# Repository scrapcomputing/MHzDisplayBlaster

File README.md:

# MHz Display Blaster

A clone of the TD-37S 2-digit MHz display that was common in 386/486 PC cases.
It can display a Turbo and a non-Turbo number, depending on the state of the Turbo switch.
It also drives the Turbo LED accordingly.

# Assembly Tips
- Video showing the assembly of rev.0.1 PCB: https://www.youtube.com/watch?v=a4iVehn7APU
> **Warning**
> Please solder the single-row header and the resistor *before* you solder the 7-segment display

# Connecting the board to the PC
- Power: The display is powered by providing 5V to the `+` pin of J4 and GND to the `-` pin.
- Turbo Switch: The turbo switch is a 3-pin 2-way switch. Connect the common wire (middle) to `CM`, the Turbo-ON wire to `T` and the Turbo-OFF wire to `N` (J4).
- Turbo LED: The turbo LED is connected to `L` and `P` on J4. `P` is the positive.

# Display Configuration
- Each segment of the 7-segment display is configured individually with a jumper
- Each segment corresponds to a pin in the configuration headers
- You can short that pin with one of the neighboring state pins (forming a `T` shape) to set its state, which can be one of the following:
  1. ON when Turbo switch is OFF (jumper to position 1)
  2. ON when Turbo switch is ON (jumper to position 2)
  3. Always ON (jumper to position 3)
  4. Always OFF (no jumper)

> **Note**
> Please note that the PCB is often mounted up side down on the case.

- For a simple tutorial on how to set it up please refer to the video: https://www.youtube.com/watch?v=wNkg-e47Ex8
- [More resources on MHz Displays](https://www.minuszerodegrees.net/led_speed_display/led_speed_display.htm)

# Bill of materials

Gerber files are published in the releases: https://github.com/scrapcomputing/MHzDisplayBlaster/releases

Reference      | Quantity| Value    | Footprint/Comments
---------------|---------|----------|----------
U1             | 1       |(e.g., LTD-6440G) | 18-DIP (0.600", 15.24mm distance between top and bottom row pins) 2-Digit 7-Segment Display Common Cathode 0.56" Green
J1 J2          | 2       |Conn_02x15| Connector Male PinHeader 2x15 P2.54mm Vertical
J4             | 1       |Conn_01x07| Connector Male PinHeader 1x07 P2.54mm Vertical
R1             | 1       | >= 39 Ohm (100 Ohms recommended)| 1/4 Watt resistor. The original TD37S has a 39 Ohm resistor. But the resistor value is specific to the type of the LEDs used. The original ones operate at around 2V, so the resistor drops 3V. Higher resistor values make the display more dim, but are also better for the longevity of the LEDs in the display.
Jumpers        | 15      |          | 2.54mm pitch jumpers

# Changelist
- Rev.0.2 : Fixes polarity issue, improves info
- Rev.0.1 : Initial revision

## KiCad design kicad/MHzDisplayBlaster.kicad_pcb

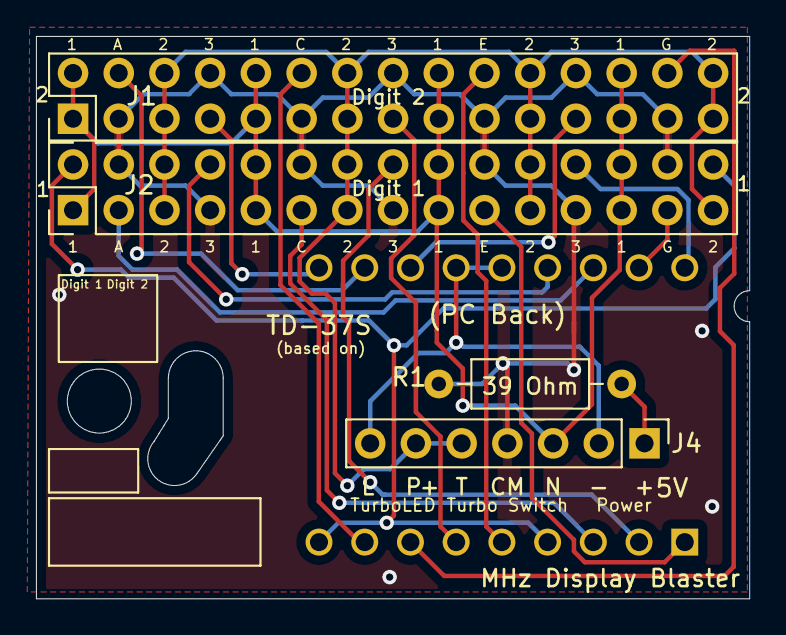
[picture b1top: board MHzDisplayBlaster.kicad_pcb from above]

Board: 2 copper layers, 39.6 x 31.2 mm, 5 parts (1 on the bottom side), 20 nets.

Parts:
J1: Conn_02x15 DigitRHS; PinHeader_2x15_P2.54mm_Vertical
J2: Conn_02x15 DigitLHS; PinHeader_2x15_P2.54mm_Vertical
J4: Conn_01x07; PinHeader_1x07_P2.54mm_Vertical
R1: 39 Ohm; R_Axial_DIN0207_L6.3mm_D2.5mm_P10.16mm_Horizontal
U1: DC56-11GWA; DA56-11CGKWA

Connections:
1: J1.1, J1.2, J1.9, J1.10, J1.17, J1.18, J1.25, J1.26, J2.1, J2.9, J2.10, J2.17, J2.18, J2.25, J2.26, J4.3
2: J1.5, J1.6, J1.13, J1.14, J1.21, J1.22, J1.29, J1.30, J2.5, J2.6, J2.13, J2.14, J2.21, J2.22, J2.29, J4.5, J4.6
3: J1.3, J1.8, J1.11, J1.16, J1.19, J1.24, J1.27, J2.4, J2.7, J2.12, J2.15, J2.20, J2.23, J2.28, J4.4, R1.1
DIG1_A: J2.3, U1.16
DIG1_B: J2.8, U1.15
DIG1_C: J2.11, U1.3
DIG1_CC: J4.2, J4.7, U1.13, U1.14
DIG1_D: J2.16, U1.2
DIG1_E: J2.19, U1.1
DIG1_F: J2.24, U1.18
DIG1_G: J2.27, U1.17
DIG2_A: J1.4, U1.11
DIG2_B: J1.7, U1.10
DIG2_C: J1.12, U1.8
DIG2_D: J1.15, U1.6
DIG2_E: J1.20, U1.5
DIG2_F: J1.23, U1.12
DIG2_G: J1.28, U1.7
DP: J2.2, J2.30, U1.4, U1.9
unnamed: J4.1, R1.2

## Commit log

2023-06-20 Rev.0.1: Initial release
2023-07-02 Rev.0.2: Fixes polarity issue, improves printed info
2023-07-05 Updates readme
2023-07-15 Improves README
2024-03-06 Adds resistor to the BOM
2025-04-18 README: Fix BOM connector 1x07
